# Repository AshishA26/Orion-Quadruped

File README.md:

# Orion — ROS2 Quadruped Robot

A custom-built 12-DOF quadruped robot designed, built, and programmed from scratch over 8 months. Uses an NVIDIA Jetson Orin Nano for high-level AI and perception, and a custom STM32 PCB for real-time low-level control.

Check out the [Demo Video](https://youtu.be/wUXvWBjLTyA)!

## Key Features

- **ROS2 / AI** — Isaac ROS Docker on Jetson Orin Nano, TensorRT for accelerated inference
- **Perception** — Stereo depth (MIDAS, SGBM) via dual CSI cameras + MediaPipe hand-pose recognition
- **SLAM & Autonomy** — RPLIDAR A1M8 with `slam_toolbox` and `nav2` for mapping and point-and-click pure-pursuit navigation
- **Embedded Control** — Custom STM32 FreeRTOS firmware: IK, walking gaits, IMU-based stabilization
- **Custom PCBs** — Multi-layer SMD boards for power distribution, servo actuation, and sensor interfacing
- **RL / Sim** — PPO training (RSL RL) in NVIDIA Isaac Lab, flat and rough terrain environments
- **Robot Eyes** — Expressive OLED eye animations via a custom Python/OpenCV node

---

## Software Architecture

**[Jetson — Isaac ROS Workspace](./Software/Jetson/workspace/isaac_ros-dev/README.md)**

| Package | Description |
|:--------|:------------|
| `orion_base` | STM32 UART bridge, joystick parser, command mux, robot eyes, joint state republisher |
| `orion_camera` | Dual CSI GStreamer node, MIDAS/SGBM depth, MediaPipe hand pose |
| `orion_lidar` | RPLIDAR A1M8 driver, `slam_toolbox` |
| `orion_navigation` | `nav2`, Pure-Pursuit path following |
| `orion_bringup` | Launch files, Docker config, systemd auto-start |
| `orion_msgs` | Custom messages: motion cmd, eye cmd, battery voltage, IMU, leg info |
| `orion_urdf` | URDF model with SolidWorks meshes, RViz launch |

**[STM32](./Software/STM32Firmware/README.md) · [Orion Firmware](./Software/STM32Firmware/Orion/README.md)**

- 5 FreeRTOS tasks: Real-time IK & gait control (Realtime) with 3-DOF per leg and 6-DOF body posture control, UART RX/TX with Jetson via DMA (High/Normal), IMU reading, Battery monitoring.

**[Reinforcement Learning](./Software/reinforcement-learning/README.md)**

- PPO training in Isaac Lab with flat and rough terrain environments. 
- SolidWorks → URDF → USD pipeline.

---

### Software Gallery

| LiDAR SLAM | Autonomous Navigation |
| :---: | :---: |
|  |  |
| Original Camera Feed | TensorRT Depth Map |
|  |  |
| Hand Pose Detection | Reinforcement Learning in Isaac Lab |
|  |  |

<p align="center">
    <strong>Foxglove Dashboard</strong>
</p>

---

## Electrical & Electronics

Custom multi-layer KiCad PCBs, fully SMD-assembled. Multiple I2C buses with LTC4311 active termination, extensive test pads and debug headers.

- **Control Board** — STM32F401, BNO055 IMU, PCA9685 servo driver
- **Power Board** — Battery distribution, INA3221 voltage monitoring (3 rails), high-current servo lines, battery alarm

### Electrical Gallery
| Control Board | Power Board |
| :---: | :---: |
|  |  |

| Control Board | Control Board Compute | Power Board |
| :---: | :---: | :---: |
|  |  |  |

---

## Mechanical Design

Chassis iteratively modelled in SolidWorks. 3D printed with 2-part silicone injection-molded feet. Bearings in all 12 joints. Magnetic mounts for tool-free access to internal electronics. Single-leg linear-rail test jig used to validate IK and gait before full integration.

| Main body parts | Leg Assembly & Silicone Feet |
| :---: | :---: |
|  |  |
| Inside Orion (Jetson + PCBs + Display only) | Inside Orion (including Batteries + Lidar + Cameras) |
|  |  |

---

## Repository Structure
Important directories:
```
Quadruped/
├── Software/
│   ├── Jetson/workspace/isaac_ros-dev/   # Isaac ROS Docker workspace (ROS2 packages)
│   ├── STM32Firmware/
│   │   ├── Orion/                        # Main FreeRTOS firmware (CMake + STM32CubeIDE)
│   │   └── Orion-Controls/               # Legacy PlatformIO firmware
│   ├── reinforcement-learning/           # Isaac Lab PPO training
│   ├── TestScripts/                      # Servo calibration, camera, depth mapping tests
├── models/                               # SolidWorks parts & assemblies, STL, 3MF exports → README
├── urdf/                                 # URDF iterations (ROS2, RL variants) → README
├── pcb/                                  # KiCad projects (Control Board, Power Board) → README
```

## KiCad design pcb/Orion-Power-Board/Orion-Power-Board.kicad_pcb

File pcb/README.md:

# PCB Design Files

KiCad projects for Orion's custom multi-layer PCBs.

## Boards

### [`Orion-Control-Board/`](./Orion-Control-Board/)
Houses compute and sensor interfacing.
- STM32F401 compute module
- BNO055 IMU
- PCA9685 16-channel PWM servo driver (I2C)
- Multiple I2C buses with LTC4311 active termination
- Extensive test pads and debug headers

### [`Orion-Power-Board/`](./Orion-Power-Board/)
Handles all power distribution.
- Raw Li-ion battery input and distribution
- INA3221 triple-channel voltage monitoring (front servos, rear servos, Jetson)
- High-current servo actuation lines
- Battery alarm system

### [`datasheets/`](./datasheets/)
Reference datasheets for key components: STM32F401, BNO055, PCA9685, INA3221, LTC4311, JST eXH connectors, Jetson Orin Nano carrier board, wire ampacity references.

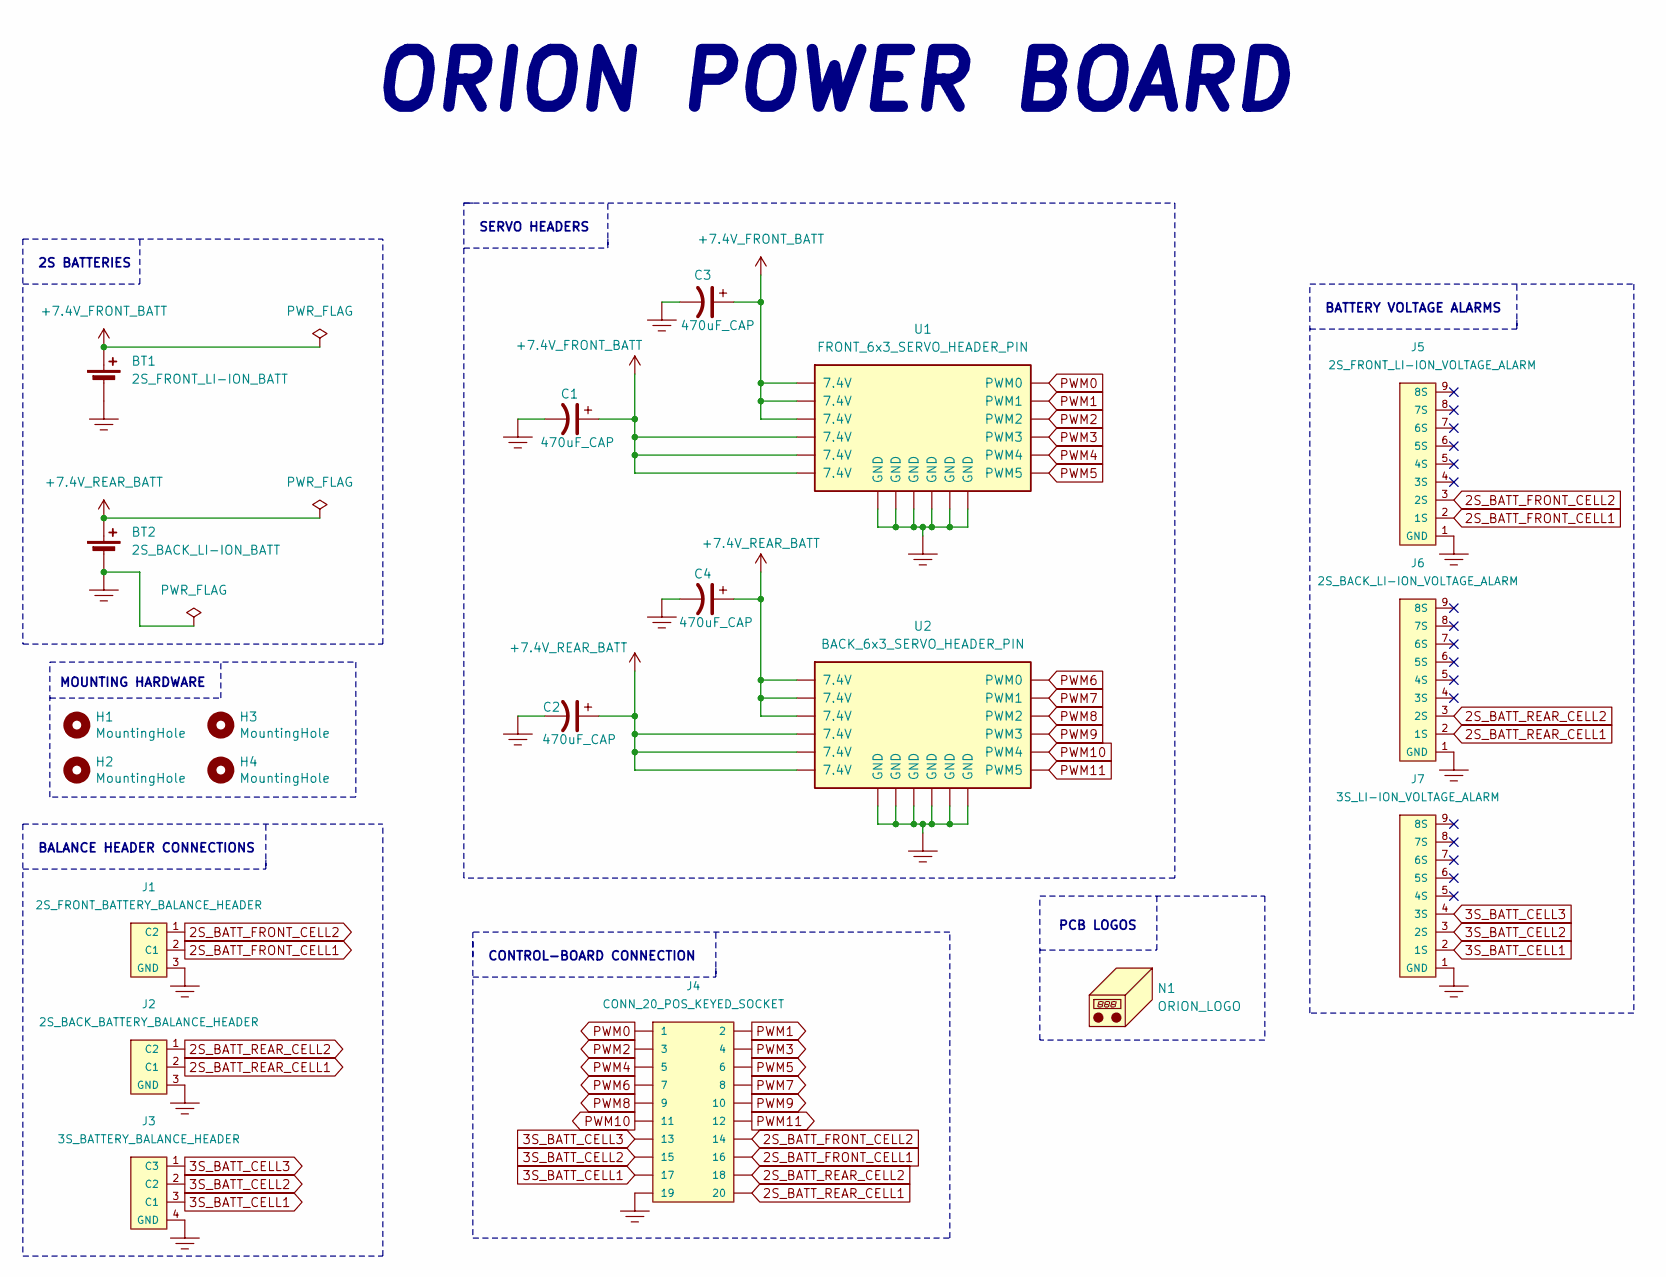
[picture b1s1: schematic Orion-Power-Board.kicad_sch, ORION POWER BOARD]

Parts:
BT1: 2S_FRONT_LI-ION_BATT; PowerPad_Pair_5.0x5.0mm_2ndPadFlipped
BT2: 2S_BACK_LI-ION_BATT; PowerPad_Pair_5.0x5.0mm_2ndPadFlipped
C1, C2, C3, C4: 470uF_CAP; CP_Radial_D8.0mm_P3.50mm
H1, H2, H3, H4: MountingHole; MountingHole_3.2mm_M3_Pad
J1: 2S_FRONT_BATTERY_BALANCE_HEADER; JST_XH_1x03_P2.54mm_Vertical
J2: 2S_BACK_BATTERY_BALANCE_HEADER; JST_XH_1x03_P2.54mm_Vertical
J3: 3S_BATTERY_BALANCE_HEADER; JST_XH_1x04_P2.54mm_Vertical
J4: CONN_20_POS_KEYED_SOCKET; SULLINS_SBH11-PBPC-D10-ST-BK_SOCKET; Manufacturer Part # SBH11-PBPC-D10-ST-BK; Digikey Part # S9172-ND
J5: 2S_FRONT_LI-ION_VOLTAGE_ALARM; LIPO_VOLTAGE_ALARM
J6: 2S_BACK_LI-ION_VOLTAGE_ALARM; LIPO_VOLTAGE_ALARM
J7: 3S_LI-ION_VOLTAGE_ALARM; LIPO_VOLTAGE_ALARM
N1: ORION_LOGO; Orion-Logo-20mm
U1: FRONT_6x3_SERVO_HEADER_PIN; Servo_PinHeader_3x06_P2.54mm_Vertical
U2: BACK_6x3_SERVO_HEADER_PIN; Servo_PinHeader_3x06_P2.54mm_Vertical

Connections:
2S_BATT_FRONT_CELL1: J1.2 (C1), J4.16, J5.2 (1S)
2S_BATT_FRONT_CELL2: J1.1 (C2), J4.14, J5.3 (2S)
2S_BATT_REAR_CELL1: J2.2 (C1), J4.20, J6.2 (1S)
2S_BATT_REAR_CELL2: J2.1 (C2), J4.18, J6.3 (2S)
3S_BATT_CELL1: J3.3 (C1), J4.17, J7.2 (1S)
3S_BATT_CELL2: J3.2 (C2), J4.15, J7.3 (2S)
3S_BATT_CELL3: J3.1 (C3), J4.13, J7.4 (3S)
+7.4V_FRONT_BATT: BT1.1 (+), C1.1, C3.1, U1.7 (7.4V), U1.8 (7.4V), U1.9 (7.4V), U1.10 (7.4V), U1.11 (7.4V), U1.12 (7.4V)
+7.4V_REAR_BATT: BT2.1 (+), C2.1, C4.1, U2.7 (7.4V), U2.8 (7.4V), U2.9 (7.4V), U2.10 (7.4V), U2.11 (7.4V), U2.12 (7.4V)
GND: BT1.2 (-), BT2.2 (-), C1.2, C2.2, C3.2, C4.2, J1.3 (GND), J2.3 (GND), J3.4 (GND), J4.19, J5.1 (GND), J6.1 (GND), J7.1 (GND), U1.13 (GND), U1.14 (GND), U1.15 (GND), U1.16 (GND), U1.17 (GND), U1.18 (GND), U2.13 (GND), U2.14 (GND), U2.15 (GND), U2.16 (GND), U2.17 (GND), U2.18 (GND)
PWM0: J4.1, U1.1 (PWM0)
PWM1: J4.2, U1.2 (PWM1)
PWM2: J4.3, U1.3 (PWM2)
PWM3: J4.4, U1.4 (PWM3)
PWM4: J4.5, U1.5 (PWM4)
PWM5: J4.6, U1.6 (PWM5)
PWM6: J4.7, U2.1 (PWM0)
PWM7: J4.8, U2.2 (PWM1)
PWM8: J4.9, U2.3 (PWM2)
PWM9: J4.10, U2.4 (PWM3)
PWM10: J4.11, U2.5 (PWM4)
PWM11: J4.12, U2.6 (PWM5)

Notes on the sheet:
BALANCE HEADER CONNECTIONS
SERVO HEADERS
ORION POWER BOARD
MOUNTING HARDWARE
2S BATTERIES
PCB LOGOS
CONTROL-BOARD CONNECTION
BATTERY VOLTAGE ALARMS

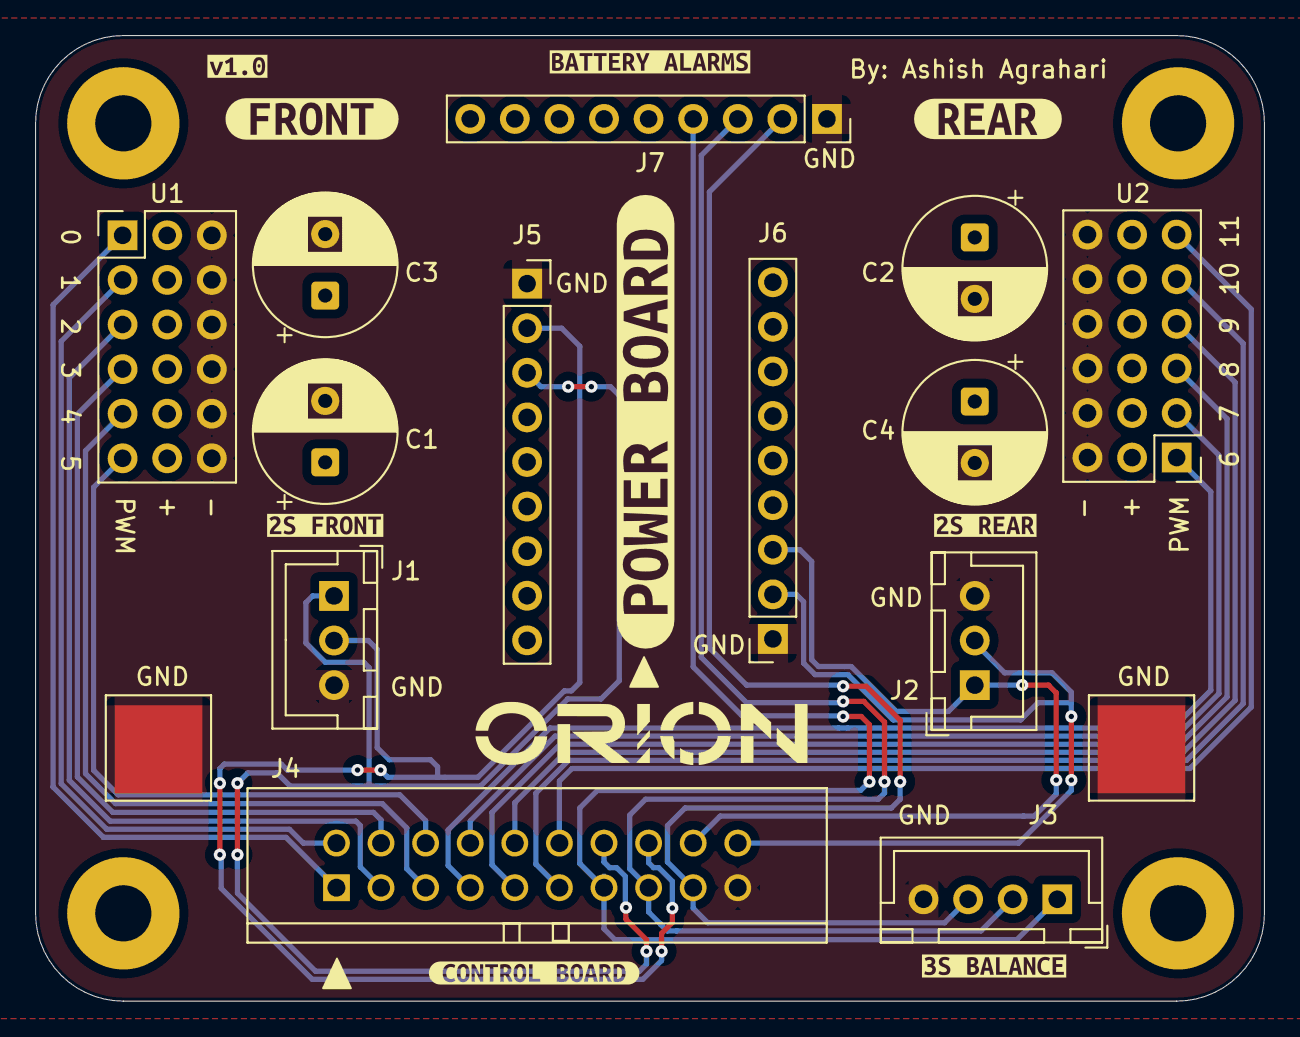
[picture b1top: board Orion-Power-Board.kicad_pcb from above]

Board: 2 copper layers, 70.0 x 55.0 mm, 29 parts (0 on the bottom side), 22 nets.

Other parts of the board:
kibuzzard-693F3E2A: G***; kibuzzard-693F3E2A
kibuzzard-693F3F14: G***; kibuzzard-693F3F14
kibuzzard-693F3F70: G***; kibuzzard-693F3F70
kibuzzard-693F65FC: G***; kibuzzard-693F65FC
kibuzzard-693F310D: G***; kibuzzard-693F310D
kibuzzard-693F552C: G***; kibuzzard-693F552C
kibuzzard-693F656E: G***; kibuzzard-693F656E
kibuzzard-693F3101: G***; kibuzzard-693F3101
kibuzzard-693F5536: G***; kibuzzard-693F5536

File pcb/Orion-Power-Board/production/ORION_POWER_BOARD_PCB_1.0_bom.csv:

Designator,Footprint,Quantity,Value,LCSC Part #
BT1,PowerPad_Pair_5.0x5.0mm_2ndPadFlipped,1,2S_FRONT_LI-ION_BATT,
BT2,PowerPad_Pair_5.0x5.0mm_2ndPadFlipped,1,2S_BACK_LI-ION_BATT,
"C1, C2, C3, C4",CP_Radial_D8.0mm_P3.50mm,4,470uF_CAP,
"H1, H2, H3, H4",MountingHole_3.2mm_M3_Pad,4,MountingHole,
J1,JST_XH_1x03_P2.54mm_Vertical,1,2S_FRONT_BATTERY_BALANCE_HEADER,
J2,JST_XH_1x03_P2.54mm_Vertical,1,2S_BACK_BATTERY_BALANCE_HEADER,
J3,JST_XH_1x04_P2.54mm_Vertical,1,3S_BATTERY_BALANCE_HEADER,
J4,SULLINS_SBH11-PBPC-D10-ST-BK_SOCKET,1,CONN_20_POS_KEYED_SOCKET,
J5,LIPO_VOLTAGE_ALARM,1,2S_FRONT_LI-ION_VOLTAGE_ALARM,
J6,LIPO_VOLTAGE_ALARM,1,2S_BACK_LI-ION_VOLTAGE_ALARM,
J7,LIPO_VOLTAGE_ALARM,1,3S_LI-ION_VOLTAGE_ALARM,
N1,Orion-Logo-20mm,1,ORION_LOGO,
U1,Servo_PinHeader_3x06_P2.54mm_Vertical,1,FRONT_6x3_SERVO_HEADER_PIN,
U2,Servo_PinHeader_3x06_P2.54mm_Vertical,1,BACK_6x3_SERVO_HEADER_PIN,

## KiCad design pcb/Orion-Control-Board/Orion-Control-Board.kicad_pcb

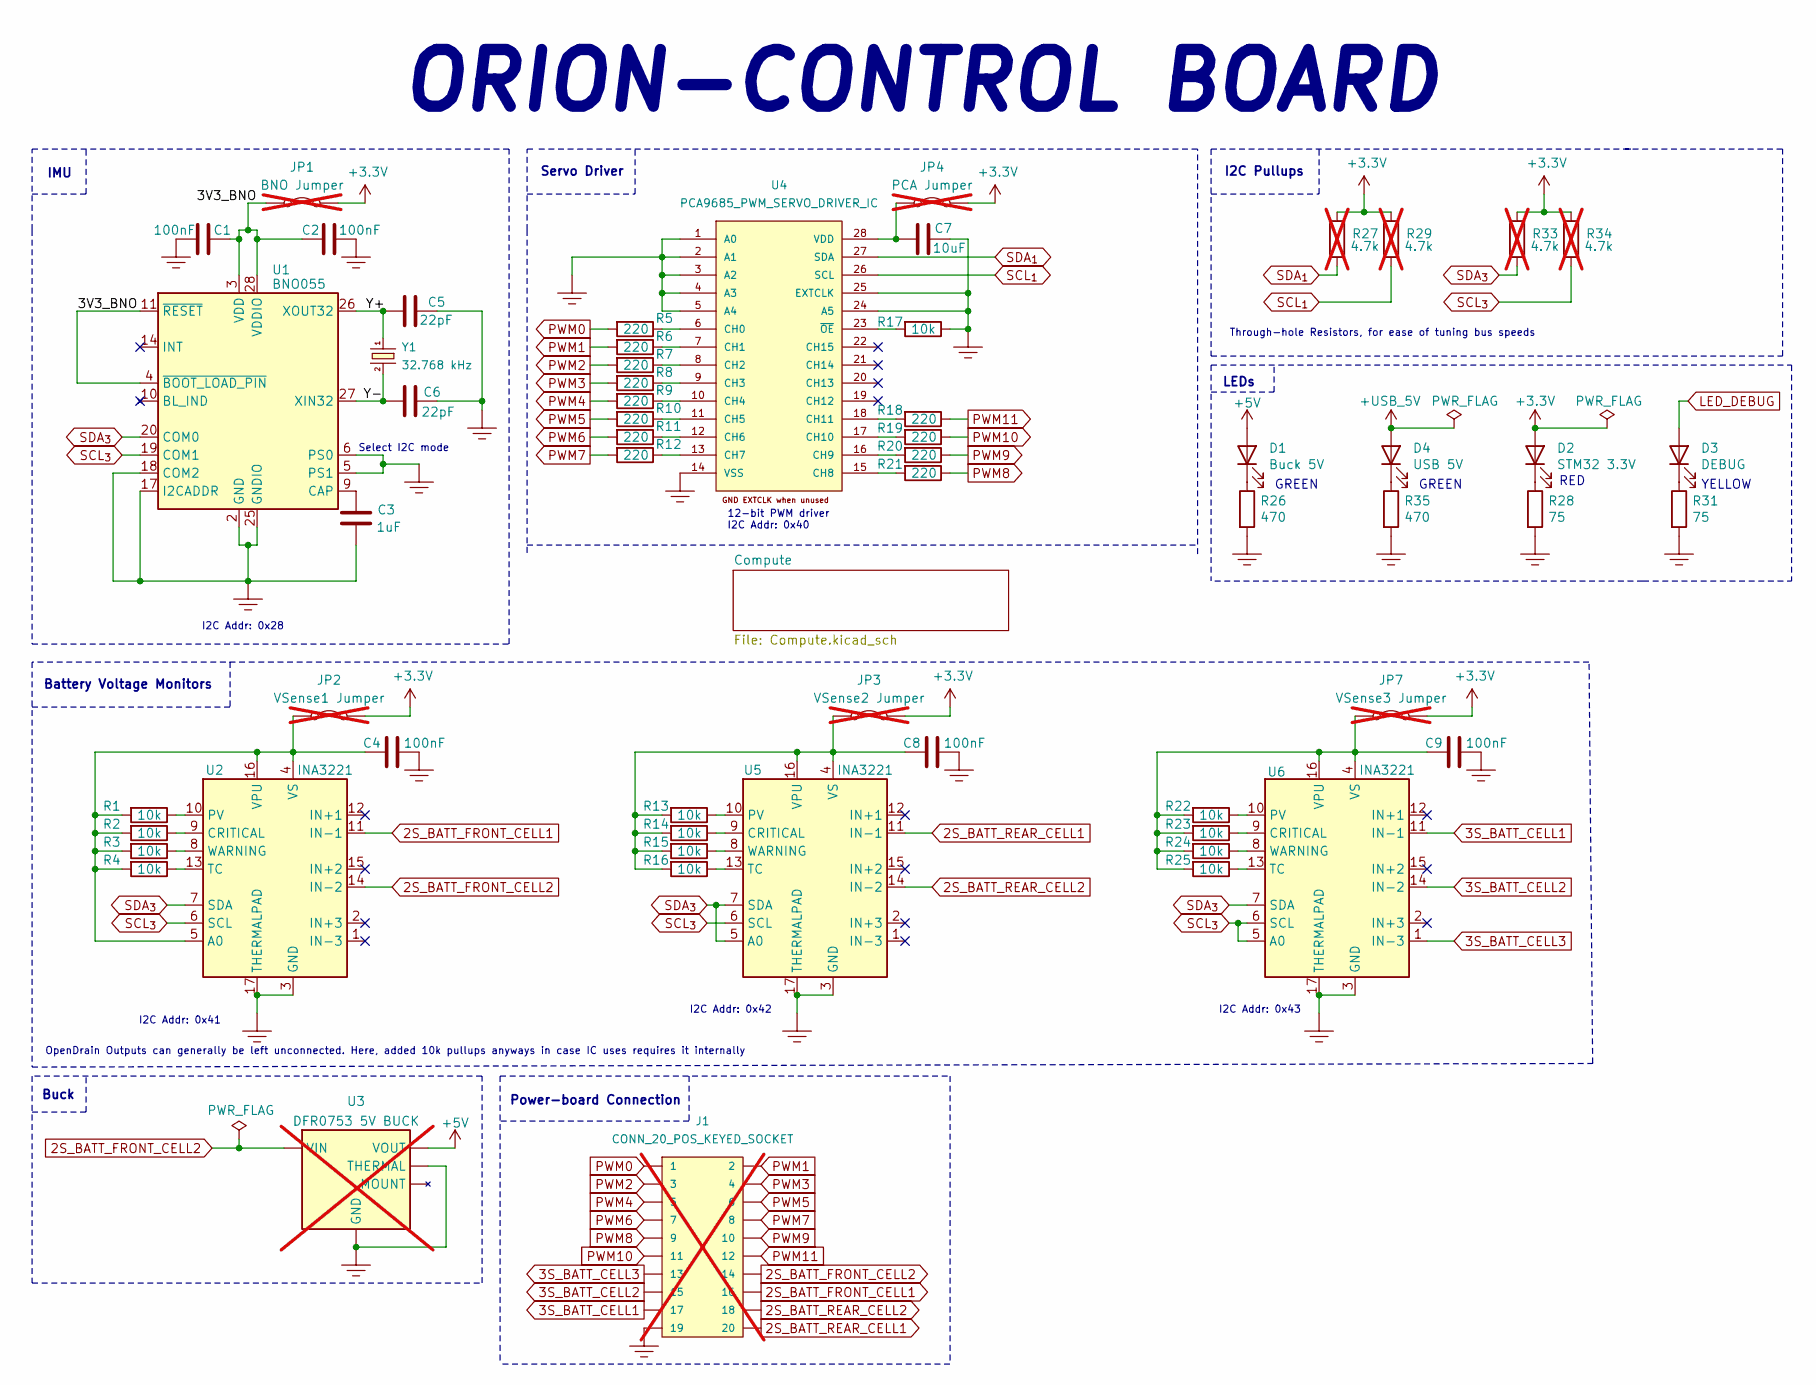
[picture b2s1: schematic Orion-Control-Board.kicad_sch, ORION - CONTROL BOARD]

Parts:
C1, C2, C4, C8, C9: 100nF; C_0603_1608Metric; JLCPCB Part # C14663
C3: 1uF; C_0603_1608Metric; JLCPCB Part # C15849
C5, C6: 22pF; C_0603_1608Metric; JLCPCB Part # C1653
C7: 10uF; C_0603_1608Metric; JLCPCB Part # C96446
D1: Buck 5V; LED_0805_2012Metric; Manufacturer Part # KT-0805G; JLCPCB Part # C2297
D2: STM32 3.3V; LED_0603_1608Metric; Manufacturer Part # KT-0603R; JLCPCB Part # C2286
D3: DEBUG; LED_0805_2012Metric; Manufacturer Part # KT-0805Y; JLCPCB Part # C2296
D4: USB 5V; LED_0805_2012Metric; Manufacturer Part # KT-0805G; JLCPCB Part # C2297
J1: CONN_20_POS_KEYED_SOCKET; SULLINS_SBH11-PBPC-D10-ST-BK_SOCKET; Manufacturer Part # SBH11-PBPC-D10-ST-BK; Digikey Part # S9172-ND; not fitted
JP1: BNO Jumper; Jumper_PinHeader_1x02_P2.54mm_Vertical_Bridged; not fitted
JP2: VSense1 Jumper; Jumper_PinHeader_1x02_P2.54mm_Vertical_Bridged; not fitted
JP3: VSense2 Jumper; Jumper_PinHeader_1x02_P2.54mm_Vertical_Bridged; not fitted
JP4: PCA Jumper; Jumper_PinHeader_1x02_P2.54mm_Vertical_Bridged; not fitted
JP7: VSense3 Jumper; Jumper_PinHeader_1x02_P2.54mm_Vertical_Bridged; not fitted
R1, R2, R3, R4, R13, R14, R15, R16, R17, R22, R23, R24, R25: 10k; R_0603_1608Metric; JLCPCB Part # C25804
R5, R6, R7, R8, R9, R10, R11, R12, R18, R19, R20, R21: 220; R_0603_1608Metric; JLCPCB Part # C22962
R26, R35: 470; R_0603_1608Metric; JLCPCB Part # C23179
R27, R29, R33, R34: 4.7k; R_SS_Axial_DIN0207_L6.3mm_D2.5mm_P10.16mm_Horizontal; not fitted
R28, R31: 75; R_0603_1608Metric; JLCPCB Part # C4275
U1: BNO055; LGA-28_5.2x3.8mm_P0.5mm; JLCPCB Part # C93216
U2, U5, U6: INA3221; Texas_RGV0016A_VQFN-16-1EP_4x4mm_P0.65mm_EP2.1x2.1mm_Therma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; Manufacturer Part # INA3221AIRGVR; JLCPCB Part # C181255
U3: DFR0753 5V BUCK; DFR0753; Manufacturer Part # DFR0753; Digikey Part # 1738-DFR0753-ND; not fitted
U4: PCA9685_PWM_SERVO_DRIVER_IC; TSSOP-28_4MM; Manufacturer Part # PCA9685PW,118; JLCPCB Part # C2678753
Y1: 32.768 kHz; CRYSTAL-SMD-3.2X1.5MM; JLCPCB Part # C97606

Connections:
2S_BATT_FRONT_CELL1: J1.16, U2.11 (IN-1)
2S_BATT_FRONT_CELL2: J1.14, U2.14 (IN-2), U3.1 (VIN)
2S_BATT_REAR_CELL1: J1.20, U5.11 (IN-1)
2S_BATT_REAR_CELL2: J1.18, U5.14 (IN-2)
3S_BATT_CELL1: J1.17, U6.11 (IN-1)
3S_BATT_CELL2: J1.15, U6.14 (IN-2)
3S_BATT_CELL3: J1.13, U6.1 (IN-3)
+3.3V: D2.2 (A), JP1.2 (B), JP2.2 (B), JP3.2 (B), JP4.2 (B), JP7.2 (B), R27.1, R29.1, R33.1, R34.1; also elsewhere on the board
+5V: D1.2 (A), U3.3 (VOUT); also elsewhere on the board
+USB_5V: D4.2 (A); also elsewhere on the board
/3V3_BNO: C1.2, C2.1, JP1.1 (A), U1.3 (VDD), U1.4 (~BOOT_LOAD_PIN), U1.11 (~RESET), U1.28 (VDDIO)
/Y+: C5.1, U1.26 (XOUT32), Y1.P$1 (1)
/Y-: C6.2, U1.27 (XIN32), Y1.P$2 (2)
GND: C1.1, C2.2, C3.2, C4.2, C5.2, C6.1, C7.1, C8.2, C9.2, J1.19, R17.1, R26.2, R28.2, R31.2, R35.2, U1.2 (GND), U1.5 (PS1), U1.6 (PS0), U1.17 (I2CADDR), U1.18 (COM2), U1.25 (GNDIO), U2.3 (GND), U2.17 (THERMALPAD), U3.2 (GND), U3.4 (THERMAL), U4.1 (A0), U4.2 (A1), U4.3 (A2), U4.4 (A3), U4.5 (A4), U4.14 (VSS), U4.24 (A5), U4.25 (EXTCLK), U5.3 (GND), U5.17 (THERMALPAD), U6.3 (GND), U6.17 (THERMALPAD); also elsewhere on the board
LED_DEBUG: D3.2 (A); also elsewhere on the board
unnamed: D1.1 (K), R26.1
unnamed: D2.1 (K), R28.1
unnamed: D3.1 (K), R31.1
unnamed: D4.1 (K), R35.1
unnamed: C4.1, JP2.1 (A), R1.2, R2.2, R3.2, R4.2, U2.4 (VS), U2.5 (A0), U2.16 (VPU)
unnamed: C8.1, JP3.1 (A), R13.2, R14.2, R15.2, R16.2, U5.4 (VS), U5.16 (VPU)
unnamed: C7.2, JP4.1 (A), U4.28 (VDD)
unnamed: C9.1, JP7.1 (A), R22.2, R23.2, R24.2, R25.2, U6.4 (VS), U6.16 (VPU)
unnamed: C3.1, U1.9 (CAP)
unnamed: R2.1, U2.9 (CRITICAL)
unnamed: R1.1, U2.10 (PV)
unnamed: R4.1, U2.13 (TC)
unnamed: R3.1, U2.8 (WARNING)
unnamed: R5.1, U4.6 (CH0)
unnamed: R6.1, U4.7 (CH1)
unnamed: R7.1, U4.8 (CH2)
unnamed: R8.1, U4.9 (CH3)
unnamed: R9.1, U4.10 (CH4)
unnamed: R10.1, U4.11 (CH5)
unnamed: R11.1, U4.12 (CH6)
unnamed: R12.1, U4.13 (CH7)
unnamed: R21.2, U4.15 (CH8)
unnamed: R20.2, U4.16 (CH9)
unnamed: R19.2, U4.17 (CH10)
unnamed: R18.2, U4.18 (CH11)
unnamed: R17.2, U4.23 (~OE)
unnamed: R14.1, U5.9 (CRITICAL)
unnamed: R13.1, U5.10 (PV)
unnamed: R16.1, U5.13 (TC)
unnamed: R15.1, U5.8 (WARNING)
unnamed: R23.1, U6.9 (CRITICAL)
unnamed: R22.1, U6.10 (PV)
unnamed: R25.1, U6.13 (TC)
unnamed: R24.1, U6.8 (WARNING)
PWM0: J1.1, R5.2
PWM1: J1.2, R6.2
PWM2: J1.3, R7.2
PWM3: J1.4, R8.2
PWM4: J1.5, R9.2
PWM5: J1.6, R10.2
PWM6: J1.7, R11.2
PWM7: J1.8, R12.2
PWM8: J1.9, R21.1
PWM9: J1.10, R20.1
PWM10: J1.11, R19.1
PWM11: J1.12, R18.1
SCL_{1}: R29.2, U4.26 (SCL); also elsewhere on the board
SCL_{3}: R34.2, U1.19 (COM1), U2.6 (SCL), U5.6 (SCL), U6.5 (A0), U6.6 (SCL); also elsewhere on the board
SDA_{1}: R27.2, U4.27 (SDA); also elsewhere on the board
SDA_{3}: R33.2, U1.20 (COM0), U2.7 (SDA), U5.5 (A0), U5.7 (SDA), U6.7 (SDA); also elsewhere on the board

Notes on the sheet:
Through-hole Resistors, for ease of tuning bus speeds
I2C Addr: 0x41
I2C Pullups
Select I2C mode
YELLOW
Battery Voltage Monitors
GREEN
Buck
RED
I2C Addr: 0x43
IMU
I2C Addr: 0x42
Power-board Connection
OpenDrain Outputs can generally be left unconnected. Here, added 10k pullups anyways in case IC uses requires it internally
ORION-CONTROL BOARD
Servo Driver
I2C Addr: 0x28
LEDs
12-bit PWM driver I2C Addr: 0x40

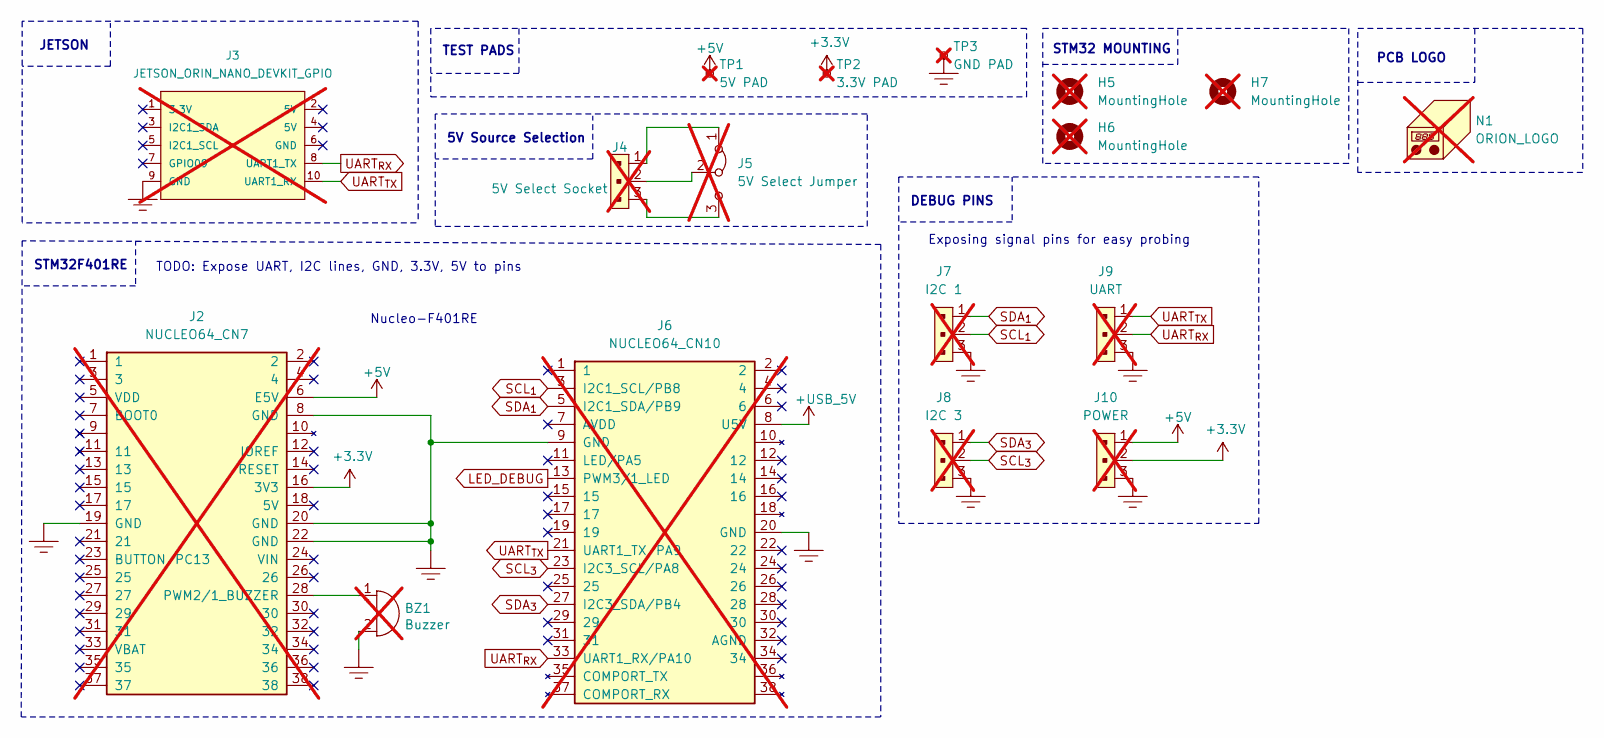
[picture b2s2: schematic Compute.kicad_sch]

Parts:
BZ1: Buzzer; Buzzer_Generic_D12.2mm_H6.5mm; not fitted
H5, H6, H7: MountingHole; MountingHole_3.2mm_M3; not fitted
J2: NUCLEO64_CN7; PinSocket_2x19_P2.54mm_Vertical; not fitted
J3: JETSON_ORIN_NANO_DEVKIT_GPIO; SULLINS_SBH11-PBPC-D05-ST-BK_SOCKET; Manufacturer Part # SBH11-PBPC-D05-ST-BK; Digikey Part # S9169-ND; not fitted
J4: 5V Select Socket; PinSocket_1x03_P2.54mm_Vertical; MPN 640456-3; Digi-Key_PN A19470-ND; not fitted
J5: 5V Select Jumper; Jumper_PinHeader_1x03_P2.54mm_Vertical_Bridged; not fitted
J6: NUCLEO64_CN10; PinSocket_2x19_P2.54mm_Vertical; not fitted
J7: I2C 1; PinHeader_1x03_P2.54mm_Vertical; MPN 640456-3; Digi-Key_PN A19470-ND; not fitted
J8: I2C 3; PinHeader_1x03_P2.54mm_Vertical; MPN 640456-3; Digi-Key_PN A19470-ND; not fitted
J9: UART; PinHeader_1x03_P2.54mm_Vertical; MPN 640456-3; Digi-Key_PN A19470-ND; not fitted
J10: POWER; PinHeader_1x03_P2.54mm_Vertical; MPN 640456-3; Digi-Key_PN A19470-ND; not fitted
N1: ORION_LOGO; Orion-Logo-20mm; not fitted
TP1: 5V PAD; TestPoint_Pad_5.0x5.0mm; not fitted
TP2: 3.3V PAD; TestPoint_Pad_5.0x5.0mm; not fitted
TP3: GND PAD; TestPoint_Pad_5.0x5.0mm; not fitted

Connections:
+3.3V: J2.16 (3V3), J10.2, TP2.1; also elsewhere on the board
+5V: J2.6 (E5V), J10.1, TP1.1; also elsewhere on the board
+USB_5V: J6.8 (U5V); also elsewhere on the board
GND: BZ1.2 (-), J2.8 (GND), J2.19 (GND), J2.20 (GND), J2.22 (GND), J3.9 (GND), J6.9 (GND), J6.20 (GND), J7.3, J8.3, J9.3, J10.3, TP3.1; also elsewhere on the board
LED_DEBUG: J6.13 (PWM3/1_LED); also elsewhere on the board
unnamed: BZ1.1 (+), J2.28 (PWM2/1_BUZZER)
unnamed: J4.1, J5.1 (A)
unnamed: J4.3, J5.3 (B)
unnamed: J4.2, J5.2 (C)
SCL_{1}: J6.3 (I2C1_SCL/PB8), J7.2; also elsewhere on the board
SCL_{3}: J6.23 (I2C3_SCL/PA8), J8.2; also elsewhere on the board
SDA_{1}: J6.5 (I2C1_SDA/PB9), J7.1; also elsewhere on the board
SDA_{3}: J6.27 (I2C3_SDA/PB4), J8.1; also elsewhere on the board
UART_{RX}: J3.8 (UART1_TX), J6.33 (UART1_RX/PA10), J9.2
UART_{TX}: J3.10 (UART1_RX), J6.21 (UART1_TX/PA9), J9.1

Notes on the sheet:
Nucleo-F401RE
STM32 MOUNTING
STM32F401RE
TEST PADS
JETSON
5V Source Selection
TODO: Expose UART, I2C lines, GND, 3.3V, 5V to pins
DEBUG PINS
PCB LOGO
Exposing signal pins for easy probing

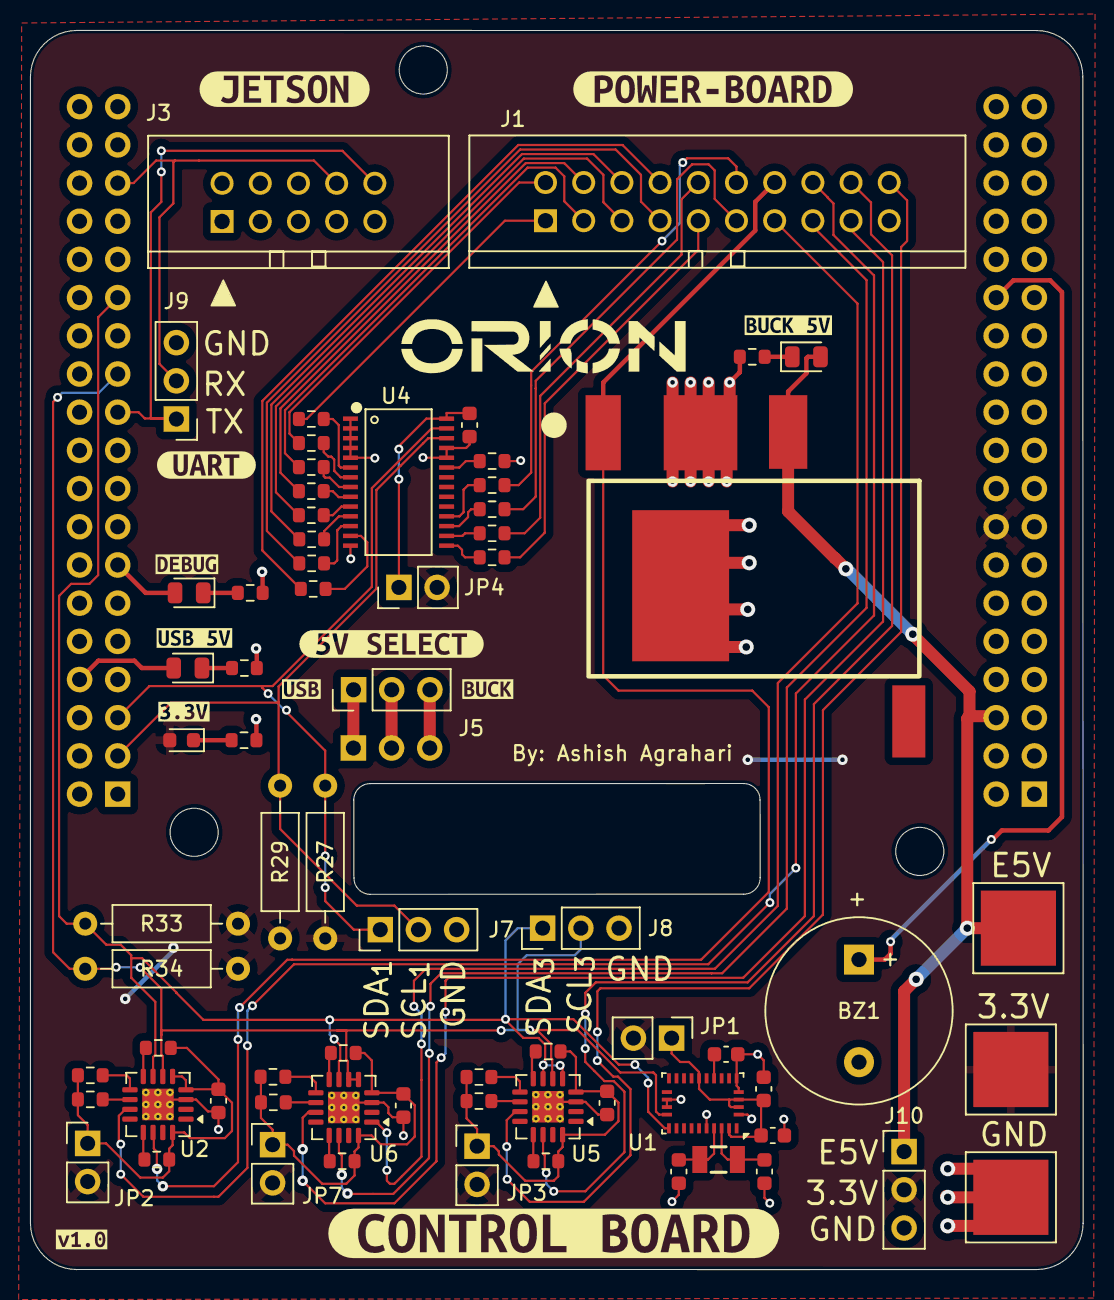
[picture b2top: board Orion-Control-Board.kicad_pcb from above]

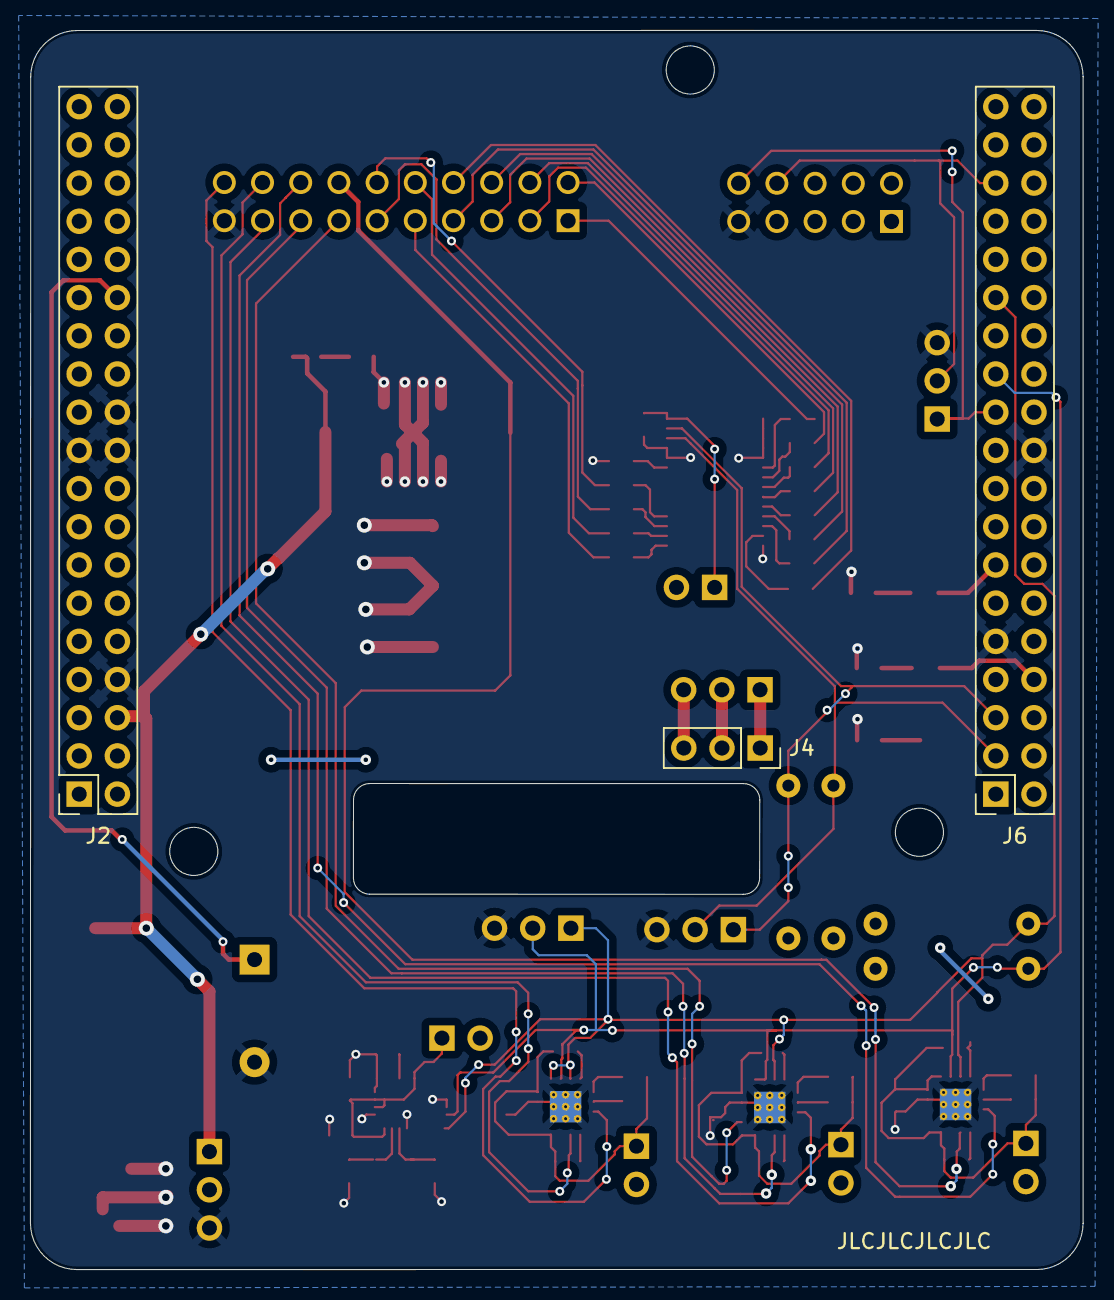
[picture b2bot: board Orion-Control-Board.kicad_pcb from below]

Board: 2 copper layers, 70.0 x 82.4 mm, 88 parts (3 on the bottom side), 71 nets.

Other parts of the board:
kibuzzard-693EFB3F: G***; kibuzzard-693EFB3F
kibuzzard-693EFB08: G***; kibuzzard-693EFB08
kibuzzard-693EFB23: G***; kibuzzard-693EFB23
kibuzzard-693EFDDB: G***; kibuzzard-693EFDDB
kibuzzard-693EFDEF: G***; kibuzzard-693EFDEF
kibuzzard-693EFDF9: G***; kibuzzard-693EFDF9
kibuzzard-693EFF71: G***; kibuzzard-693EFF71
kibuzzard-693F00A5: G***; kibuzzard-693F00A5
kibuzzard-693F01AF: G***; kibuzzard-693F01AF
kibuzzard-693F01CD: G***; kibuzzard-693F01CD
kibuzzard-693F1F19: G***; kibuzzard-693F1F19
kibuzzard-693F6234: G***; kibuzzard-693F6234

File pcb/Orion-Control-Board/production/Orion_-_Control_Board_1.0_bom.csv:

Designator,Footprint,Quantity,Value,LCSC Part #
"C1, C2, C4, C8, C9",0603,5,100nF,C14663
C3,0603,1,1uF,C15849
"C5, C6",0603,2,22pF,C1653
C7,0603,1,10uF,C96446
D1,0805,1,Buck 5V,C2297
D2,0603,1,STM32 3.3V,C2286
D3,0805,1,DEBUG,C2296
D4,0805,1,USB 5V,C2297
"R1, R13, R14, R15, R16, R17, R2, R22, R23, R24, R25, R3, R4",0603,13,10k,C25804
"R10, R11, R12, R18, R19, R20, R21, R5, R6, R7, R8, R9",0603,12,220,C22962
"R26, R35",0603,2,470,C23179
"R28, R31",0603,2,75,C4275
U1,LGA-28_5.2x3.8mm_P0.5mm,1,BNO055,C93216
"U2, U5, U6",Texas_RGV0016A_VQFN-16-1EP_4x4mm_P0.65mm_EP2.1x2.1mm_ThermalVias,3,INA3221,C181255
U4,TSSOP-28_4MM,1,PCA9685_PWM_SERVO_DRIVER_IC,C2678753
Y1,CRYSTAL-SMD-3.2X1.5MM,1,32.768 kHz,C97606

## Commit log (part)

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2025-11-10 Working on femur
2025-11-10 Mostly done femur
2025-11-17 Done femur
2025-11-19 Fixing femur
2025-11-21 Working on tibia
2025-11-22 Tibia in progress
2025-11-23 Almost done main leg
2025-11-24 Finished bellcrank
2025-11-26 Updated servo arm size
2025-11-30 Foot mold
2025-11-30 Update naming
2025-12-01 Add leg servo holder
2025-12-02 Almost done leg servo holder
2025-12-11 Test code and fixed mold model
2025-12-11 Moved stl files
2025-12-11 Made leg jump
2025-12-12 Add Control board
2025-12-12 Add linear rail design
2025-12-12 Initial power board
2025-12-13 Design IMU, Voltage Sensor, and Driver circuits
2025-12-13 Add lipo tester and LTC extender
2025-12-13 Power board
2025-12-14 Complete Schematic - Add STM32
2025-12-14 Update JLCPCB rules
2025-12-14 Done layout of power board
2025-12-14 Update symbols
2025-12-14 Route IMU and Servo Driver
2025-12-14 Update power board
2025-12-14 Gitignore
2025-12-14 Route more
2025-12-14 Route most traces
2025-12-14 Almost finished power board
2025-12-14 Route all except voltage sensor
2025-12-15 Finished power board
2025-12-15 Finish Control board
2025-12-15 Round slot outline
2025-12-15 Review Power board.
2025-12-15 Add fab outputs
2025-12-15 Finalize Fab outputs
2025-12-17 Made 2 parts, attempting to fix assembly
2025-12-17 Redid assembl
2025-12-18 Assembly before duplicate
2025-12-18 Add screen step model
2025-12-18 Cleaning up models
2025-12-18 Create CubeMX project and test in VSCode
2025-12-19 Add Jetson and PCB models
2025-12-20 Working on body
2025-12-20 Trying to reduce assembly size
2025-12-21 Lidar
2025-12-21 Fixed solidworks assembly size
2025-12-22 Fixed appearance of quadruped
2025-12-23 Fixing linkages and body
2025-12-24 Fix linages
2025-12-24 Testing
2025-12-24 Done legs
2025-12-25 Adjust for servo holder bearing
2025-12-26 magnets
2025-12-26 Fixed lidar model
2025-12-26 Start sim
2025-12-26 Rename files
2025-12-26 Cleanup sim trials
2025-12-27 servo clock scripts
2025-12-27 Add lidar holder
2025-12-28 Bearing Dimensions from testing
2025-12-28 Working on lidar and camera holder
2025-12-28 Finish Jetson Case
2025-12-28 Adjusting for bearings
2025-12-28 stls
2025-12-29 Fixed appearance
2025-12-29 Fix rear top plate
2025-12-29 Added orion logo
2025-12-29 Finished front half
2025-12-29 Fixing bottom of body and adding rear shelf
2025-12-30 Fix Servo Clocking Script
2025-12-30 Mechanical done
2025-12-30 Done mechanical
2025-12-30 Test x axis of single leg
2025-12-30 rebuild
2025-12-30 Create and test semicircle gait
    - x and z position control works
2025-12-30 Add roboeyes scripts
2025-12-30 STL for bottom of body
2025-12-31 Update back plate and print coupler
2025-12-31 Rear body stl
2025-12-31 Fixed front lid
2025-12-31 Exported stl files for shelf and top lid
2025-12-31 Schematic note
2025-12-31 Fixed lego servo holder parts
2025-12-31 Exported camera holder stl
2026-01-01 Initialize control proj
2026-01-01 Fix camera holder
2026-01-03 Test one leg in main control code
2026-01-03 Tuning front left leg on dog
2026-01-04 Move legs in unison
2026-01-04 Make constant variables
2026-01-04 Add in working trotting gait
2026-01-04 Added offset to hip servos
2026-01-04 Add fullscreen version of eyes
2026-01-04 jetson instructions
2026-01-04 Edit eyesize for jetson screen
2026-01-07 clocking script
2026-01-07 Servo calibration
2026-01-07 Recalibrate servos
2026-01-07 Add heeling and standing poses
2026-01-07 Depth scripts
2026-01-08 Calibrated stereo camera and got lidar working in docker ros2 container
2026-01-09 save stereo images
2026-01-09 Testing midas
2026-01-09 Getting left and right
2026-01-09 midas
2026-01-11 Update roboeyes and ros lidar setup
2026-01-11 Update walking params
2026-01-11 Organized files
2026-01-15 Add chessboard pattern
2026-01-15 Updating readme with photos
2026-01-15 Update schematics
2026-01-16 Update readme photos with a few thumbnails
2026-01-16 Update schematic location
2026-01-16 Updating readme with inside pics
2026-01-19 Attempting explode in solidworks
2026-01-21 Update link
2026-01-22 Update readme tables
2026-04-25 Fixed hip calculation
2026-04-26 Updated center positions
2026-04-26 Sine step gait
2026-04-28 Script to center all servos
2026-04-29 Enabled freertos
2026-04-29 LED blink
2026-04-29 Updated libraries and fix led blink
2026-04-30 PCA driver and i2c lines
2026-04-30 PCA Driver works and servos are centered with configs
2026-05-01 Added inverse kinematics, and leg gaits
2026-05-01 Fixed hip if statements
2026-05-01 Fixed comment, and added linkage 3mf file
2026-05-01 Enabled rtos fpu for floating point calcs
2026-05-01 Working on orientation matrix
2026-05-01 Fixed jitter by speeding up sin wave movement
2026-05-01 Cleaning up orientation code
2026-05-02 Reformatted code to make sense
2026-05-05 Trying wave pose
2026-05-05 Testing wave
2026-05-05 Waving fixed
2026-05-13 Added IMU init and read orientation code
2026-05-24 Did axis remapping to match dogs orientation
2026-05-24 Update consts
2026-05-24 Exaggerate waving pose
2026-05-24 Created orion_base package for jetson comms
2026-05-25 Fix ths1 issues (connection uart)
2026-05-25 Add option to choose either keyboard or joystick
2026-05-30 Update joy index
2026-05-30 Added dma support to usart1
2026-05-30 Added code for reading in jetson data
2026-05-30 Update comments
2026-05-30 Update vel
2026-05-30 Add comment
2026-05-30 Added comments for explaination
2026-05-31 Added tasks, splitting up code now
2026-05-31 Split into tasks
2026-05-31 Safety feature to stop dog incase disconnection
2026-05-31 Going to test out execute gait
2026-05-31 Added and tested holonomic drive
2026-06-05 Add eyes run command in readme
2026-06-05 Add orion bringup
2026-06-06 Increasing controlability with joystick
2026-06-06 Fix bugs in button map
2026-06-06 Fixing controls
2026-06-06 Fixed messy controls
2026-06-06 Now reflecting changes in stm side
2026-06-06 Fix z pos
2026-06-06 Comment out prints
2026-06-06 Added RTOS functions and commands for numerous control options
2026-06-07 Updated xy offset value
2026-06-07 Rtos compatibility
2026-06-17 Attempt to fix dog getting stuck in tilt position
2026-06-23 Fixed RTOS waving gait
2026-06-23 Added pivot to updateBodyPostureWithFeet()
2026-06-23 Fix waving commands to set tibia angle.
2026-06-23 Clean up empty lines
2026-06-23 Fixed reset cmd to not require deadman switch, fixed tilt up down cmd
2026-06-24 Cleaned up bridge node code into operation functions
2026-06-28 Added base roboeyes node
2026-06-29 Fix gitignore xml files and create orion msgs package
2026-06-29 Refactoring code from stm32 bridge node to joystick parser node
2026-06-30 Add param yamls to all packages. and topic remapping. Added base cmd_mux node
